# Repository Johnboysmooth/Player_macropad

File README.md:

# Player! V1.2

Player! is a five button macropad originally designed to accomodate changing music settings in Spotify without tabbing into the Spotify client. By default it is programmed to use the built-in media keys in Windows, which can be further optimised with global hotkeys using [Toastify](https://github.com/aleab/toastify).

Using four cherry compatible switches, Player! provides dedicated keys for pausing/playing music -  returning to a previous song, and skipping to the next song. The fourth switch remains user programmable, binded to 'insert' by default to be used as dedicated Discord mute key. A rotary encoder allows for volume control, with a toggle function bound to its embedded switch to allow rotary control of rewinding and fast-forwarding music.
# Images

# [Bill of Materials](https://octopart.com/bom-tool/iGNVRgwb)

# Bootloader Information

The Player! uses a usb bootloader which allows the ATMega328 to program itself with QMK, namely USBaspLoader.

The custom bootloader was adapted from [coseyfannitutti](https://github.com/coseyfannitutti)'s, changing a few pin definitions, programmer choice and adding a port definiton for avrdude in my setup. 

* The bootloader is available [here](https://github.com/Johnboysmooth/USBaspLoader).
* The instructions for setting up the build environment can be found in the readme.
* Some changes may be required, such as changing the port or programmer definitions for your setup, which can be found on lines 9 and 44 of the makefile.inc respectively. **Never** edit the makefile directly.
* Flashing the ATMega328 once the build environment is setup:

	```make flash``` (flashes the makefile)

	```make fuse``` (sets fuses for ATMega328)

Assuming the flash was successful, it should now be possible to return the microcontroller to the Player! PCB and flash the firmware via the USB connection.

# Firmware 
Player! supports either [Vial](https://get.vial.today/) or [VIA](https://www.caniusevia.com/) for rebinding keys. It is recommended to use Vial to allow rebinding of the rotary encoder, and avoid additional steps required in VIA.

### Entering bootloader mode
Player! will need to be put into bootloader mode to allow QMK to be flashed via the USB connection, see below:

1. Press and hold ```Boot``` switch
2. Tap ```Reset``` switch
3. Release ```Boot``` switch

USBaspLoader will show up in device manager or as a connected device in QMK toolbox when the device has successfully entered bootloader mode, like so:

## Vial Support (Recommended)

Vial compatible firmware can be flashed to the Player! using the [player_vial.hex](/Firmware). 
1. In QMK_Toolbox, click "Open", then navigate to player_vial.hex and select it. 
2. Click "Flash". 
3. Following successful flash completion, press the ```Reset``` button on the PCB. 

The Player! can now be configured and is now ready to use. The rotary encoder is rebound using the two circular icons on the top row.

*A current bug means the second layer is incorrectly labelled, however it maintains functionality.

### VIA Support (Not Recommended)

VIA compatible firmware can also be flashed to the Player! using the [player_via.hex](/Firmware), however an additional step is required.
1. In QMK_Toolbox, click "Open" then navigate to player_vial.hex and select it.
2. Click "Flash". 
3. Following successful flash completion, press the ```Reset``` button on the PCB. 
4. After opening the VIA window, navigate to the "Design" tab (which may require enabling in settings) and upload the playerkeymap.json. 

Going back to the Configure tab in VIA, the Player! can be configured and is now ready to use.

### Default Configuration

It is not required to use Vial or VIA when using the Player!, the default keymap can be flashed using the [player_default.hex](/Firmware). 
1. In QMK_Toolbox, click "Open" and navigate to player_default.hex and click "Flash".
2. Following successful flash completion, press the ```Reset``` button on the PCB. 

The Player! is now ready to use.

## License
<br />Player! is licensed under a <a rel="license" href="http://creativecommons.org/licenses/by-nc/4.0/">Creative Commons Attribution-NonCommercial 4.0 International License </a>

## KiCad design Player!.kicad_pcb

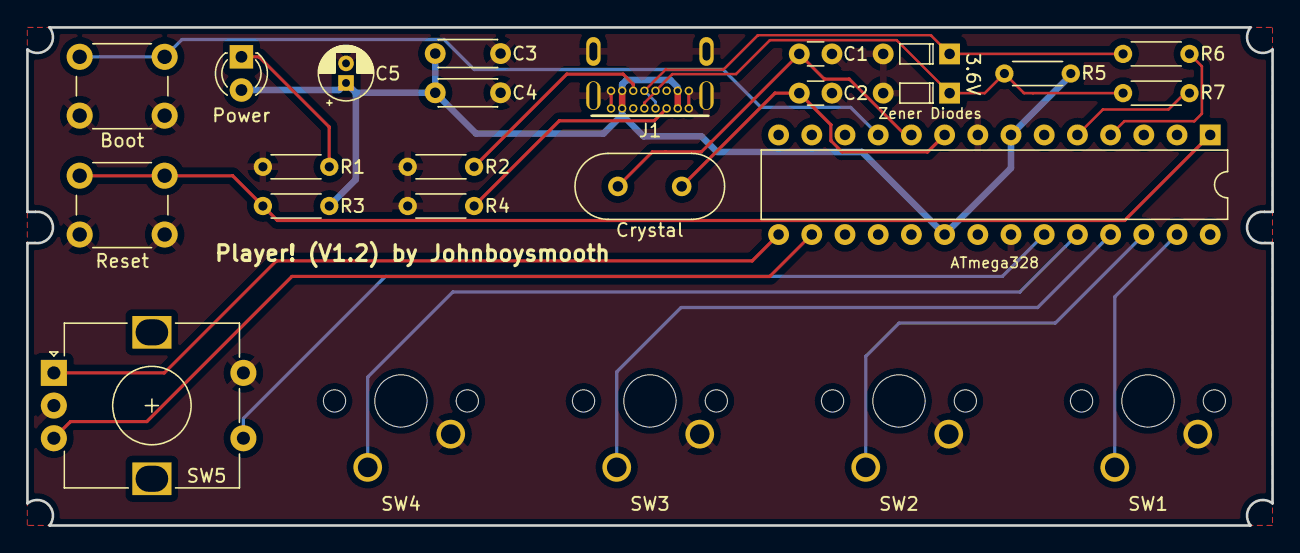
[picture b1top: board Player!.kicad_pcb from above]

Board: 2 copper layers, 95.2 x 38.1 mm, 25 parts (0 on the bottom side), 20 nets.

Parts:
ATmega328: ATmega328P-P; ATmega328p DIP-28
Boot: BOOT; SW_PUSH_6mm
C1, C2: 22p; C_Disc_D3.0mm_W1.6mm_P2.50mm
C3, C4: 0.1u; C_Disc_D4.3mm_W1.9mm_P5.00mm
C5: 4.7u; CP_Radial_D4.0mm_P1.50mm
Crystal1: Crystal; Crystal_HC49-4H_Vertical
DN1: 3.6V; D_DO-35_SOD27_P5.08mm_Horizontal
DP1: 3.6V; D_DO-35_SOD27_P5.08mm_Horizontal
J1: USB4085-GF-A_REVA4; GCT_USB4085-GF-A_REVA4
Power: POWERLED; LED_D3.0mm
R1: 1.5k; R_Axial_DIN0204_L3.6mm_D1.6mm_P5.08mm_Horizontal
R2, R4: 5.1k; R_Axial_DIN0204_L3.6mm_D1.6mm_P5.08mm_Horizontal
R3: 10K; R_Axial_DIN0204_L3.6mm_D1.6mm_P5.08mm_Horizontal
R5: 1.5K; R_Axial_DIN0204_L3.6mm_D1.6mm_P5.08mm_Horizontal
R6, R7: 75; R_Axial_DIN0204_L3.6mm_D1.6mm_P5.08mm_Horizontal
Reset: RESET; SW_PUSH_6mm
SW1, SW2, SW3, SW4: SW_Push; Player! 1u PCB
SW5: RotaryEncoder_Switch; RotaryEncoder_Alps_EC12E-Switch_Vertical_H20mm

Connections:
+5V: ATmega328.7 (VCC), ATmega328.20 (AVCC), C3.1, C4.1, C5.1, J1.A4 (VBUS), J1.A9 (VBUS), J1.B4 (VBUS), J1.B9 (VBUS), Power.2 (A), R3.1, R5.1
/BOOT: ATmega328.11 (PD5), Boot.1
/CC1: J1.A5 (CC1), R4.1
/CC2: J1.B5 (CC2), R2.1
/DN: DP1.1 (K), J1.A7 (DN1), J1.B7 (DN2), R5.2, R7.1
/DP: DN1.1 (K), J1.A6 (DP1), J1.B6 (DP2), R6.1
/LED: Power.1 (K), R1.1
/RST: ATmega328.1 (~RESET/PC6), R3.2, Reset.1
/XTAL1: ATmega328.9 (XTAL1/PB6), C2.1, Crystal1.2
/XTAL2: ATmega328.10 (XTAL2/PB7), C1.1, Crystal1.1
D+: ATmega328.4 (PD2), R6.2
D-: ATmega328.5 (PD3), R7.2
GND: ATmega328.8 (GND), ATmega328.22 (GND), Boot.2, C1.2, C2.2, C3.2, C4.2, C5.2, DN1.2 (A), DP1.2 (A), J1.A1 (GND), J1.A12 (GND), J1.B1 (GND), J1.B12 (GND), J1.P1 (SHELL), J1.P2 (SHELL), J1.P3 (SHELL), J1.P4 (SHELL), R1.2, R2.2, R4.2, Reset.2, SW1.2, SW2.2, SW3.2, SW4.2, SW5.C, SW5.S1
ROTA: ATmega328.15 (PB1), SW5.A
ROTB: ATmega328.16 (PB2), SW5.B
SW1: ATmega328.27 (PC4), SW1.1
SW2: ATmega328.26 (PC3), SW2.1
SW3: ATmega328.25 (PC2), SW3.1
SW4: ATmega328.24 (PC1), SW4.1
SW5: ATmega328.23 (PC0), SW5.S2

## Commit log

2022-06-02 Player! Macropad
    Schematics, PCB and Footprints
2022-06-02 Minor Changes for V1.1
    Altered encoder location, some minor changes to front silkscreen texts
2022-06-02 Minor text changes
2022-06-02 Added Image
2022-06-02 Backup
2022-06-07 3D Models
    Added models missing for various components, rotated PCB and text. Updated readme with images
2022-06-07 Updated Images
2022-06-07 Changed Rotary Encoder Model
2022-06-07 Repositioned LED
2022-06-07 Updated readme to include flashing information
2022-06-07 Remove backups
2022-06-08 Updated diode on 3d model
2022-06-08 Updated images with fixed diode
2022-06-08 Added a note on VIA support
2022-06-09 Included firmware files and updated readme
2022-06-09 Replaced with correct .json
2022-06-09 Changed file structure
2022-06-09 Update readme for rotary encoder in Vial
2022-06-09 Update PCB
    Updated the PCB to include new models for rotary encoder with cap, cherry keys with keycaps. Also reordered some components and added a new horizontal zener diode model
2022-06-09 Updated images to reflect new models
2022-06-09 Add bill of materials
2022-06-09 Fix text location
2022-06-09 Update images
2022-06-09 Update text position
2022-06-15 Updated Models
    Changed type C footprint & model, updated to use .step models in 3d for all components
2022-07-10 Updating PCB and Models for Case
2022-07-10 Adding Case Models
2022-07-10 Updating Images with Case
